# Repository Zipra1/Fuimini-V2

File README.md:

# This design is currently under development.
I do not recommend making this at the moment.
Case is currently not finished, but it should work.

nRF52833 based smol SlimeVR tracker

Design is optimized for manufacturability at medium scales & comfort

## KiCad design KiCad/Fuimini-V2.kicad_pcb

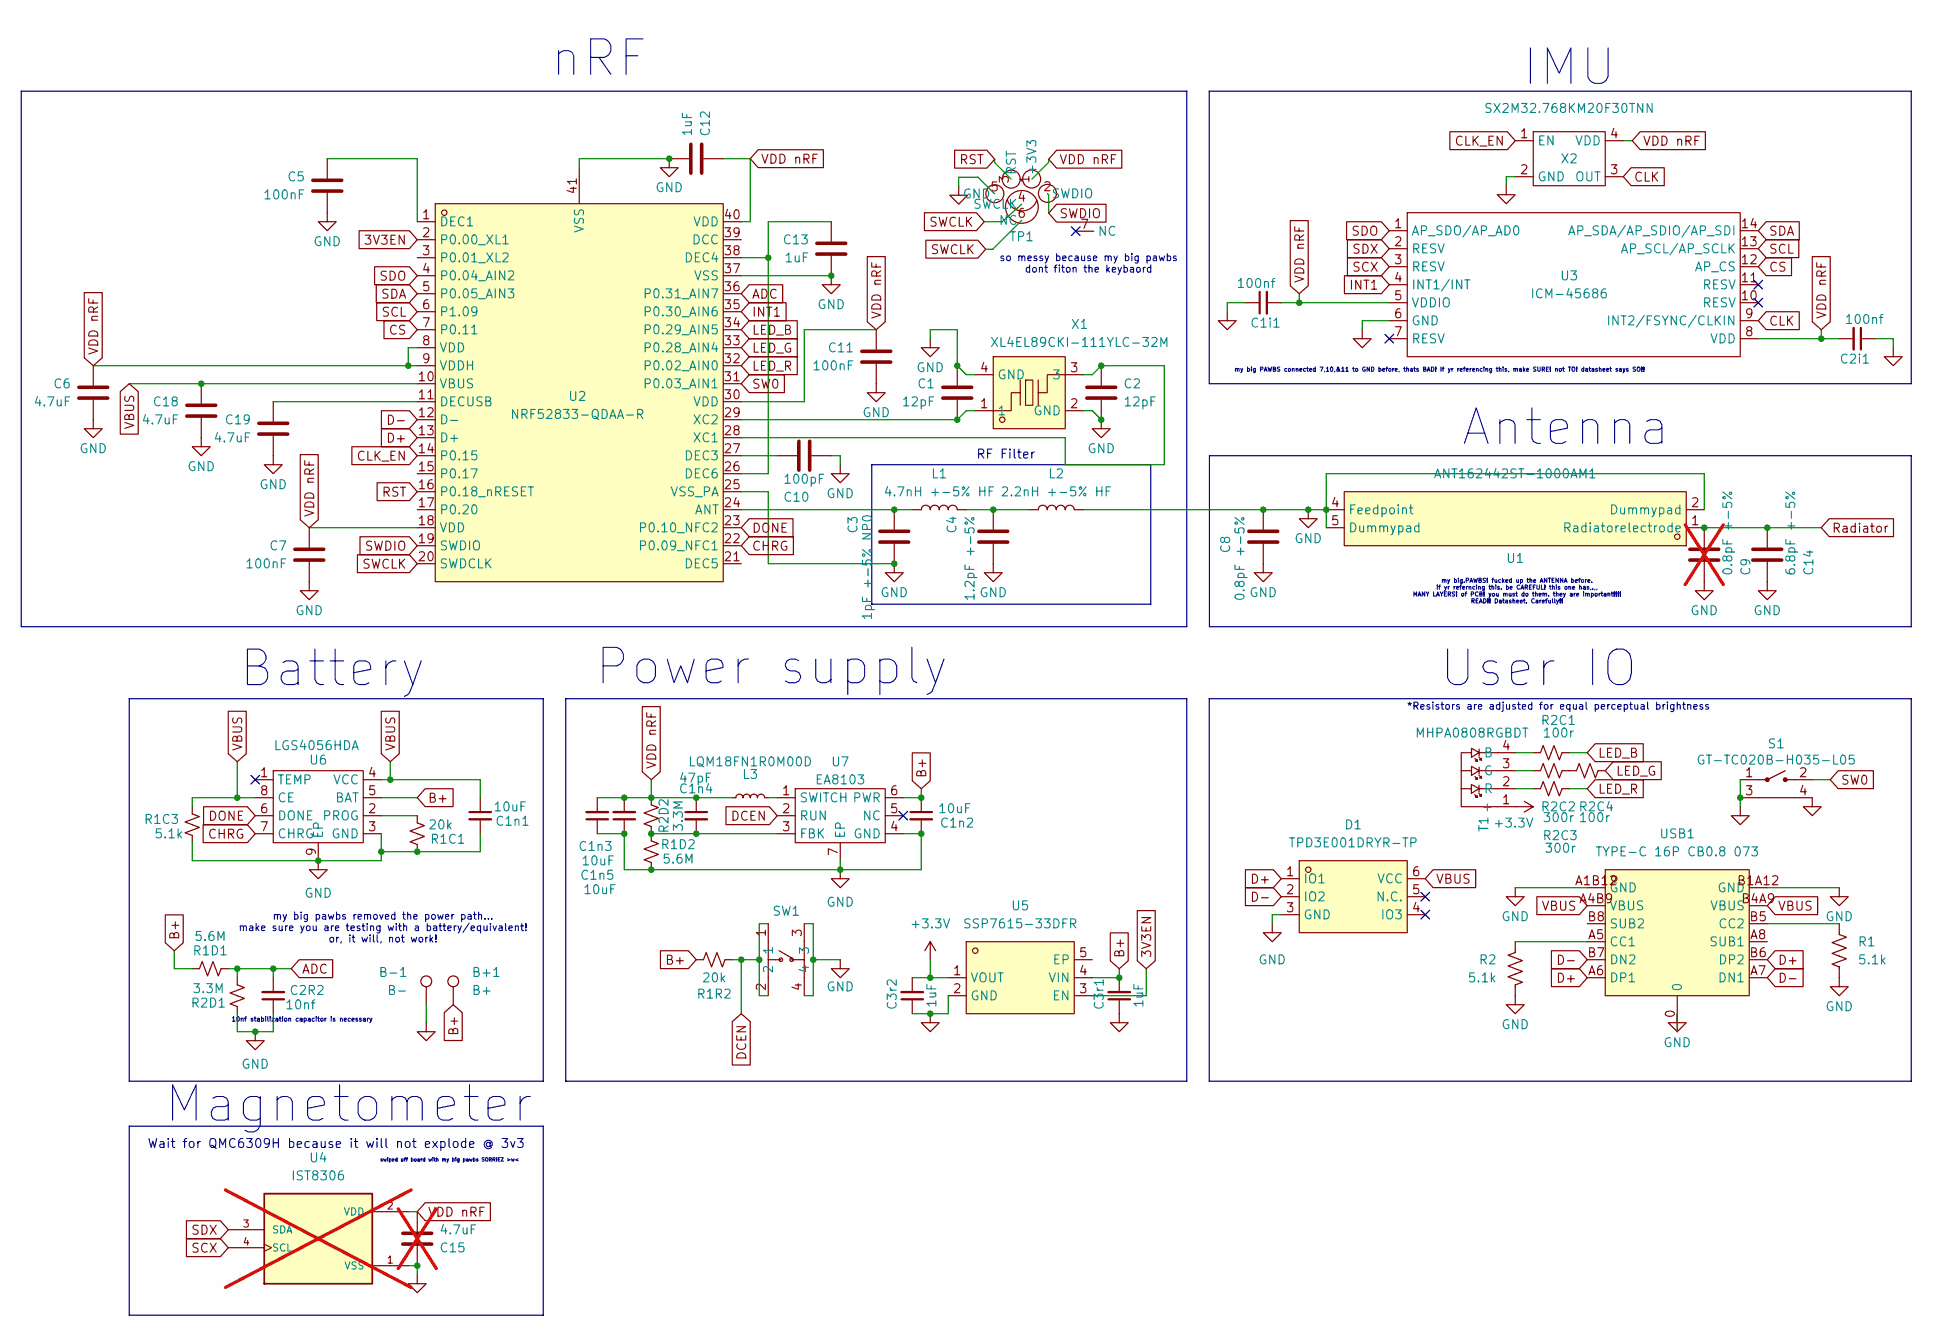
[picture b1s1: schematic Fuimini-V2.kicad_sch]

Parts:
B+1: B+; 2_3-1.5_2.5_1_1
B-1: B-; 2_3-1.5_2.5_1_1
C1, C2: 12pF; C_0201_JLC
C1i1, C2i1: 100nf; C_0201_JLC
C1n1, C1n2, C1n3, C1n5: 10uF; C_0402_JLC
C1n4: 47pF; C_0201_JLC
C2R2: 10nf; C_0201_JLC
C3: 1pF +-5% NP0; C_0201_JLC
C3r1, C3r2, C12, C13: 1uF; C_0201_JLC
C4: 1.2pF +-5%; C_0201_JLC
C5, C7, C11: 100nF; C_0201_JLC
C6, C18, C19: 4.7uF; C_0201_JLC
C8: 0.8pF +-5%; C_0201_JLC
C9: 0.8pF +-5%; C_0201_JLC; not fitted
C10: 100pF; C_0201_JLC
C14: 6.8pF +-5%; C_0201_JLC
C15: 4.7uF; C_0201_JLC; not fitted
D1: TPD3E001DRYR-TP; SON-6_L1.5-W1.0-P0.50-BL_SN74LVC1G19DRYR; LCSC Part C1973987
L1: 4.7nH +-5% HF; L_0201_0603Metric
L2: 2.2nH +-5% HF; L_0201_0603Metric
L3: LQM18FN1R0M00D; L0603
R1, R1C3, R2: 5.1k; R_0201_JLC
R1C1, R1R2: 20k; R_0201_JLC
R1D1, R1D2: 5.6M; R_0201_JLC
R2C1, R2C4: 100r; R_0201_JLC
R2C2, R2C3: 300r; R_0201_JLC
R2D1, R2D2: 3.3M; R_0201_JLC
S1: GT-TC020B-H035-L05; SW-SMD_GT-TC020B-H035-L05
SW1: 1TS026A-1100-0550-CT; SW-SMD_4P-L2.6-W1.6-P0.75-LS3.0; LCSC Part C913779
T1: MHPA0808RGBDT; LED-ARRAY-SMD_4P-L0.80-W0.80-BR
TP1: Paw-Connect_RevB_TC2030-IDC-NL_2x03_P1.27mm_Vertical
U1: ANT162442ST-1000AM1; ANT-SMD_6P-L1.6-W0.8-L; LCSC Part C5119334
U2: NRF52833-QDAA-R; QFN-40_L5.0-W5.0-P0.40-TL-EP3.6; LCSC Part C2895249
U3: ICM-45686; ICM-42688-P
U4: IST8306; PARTREV 1.4; not fitted
U5: SSP7615-33DFR; DFN-4_L1.0-W1.0-P0.65-BL-EP; LCSC Part C3011523
U6: LGS4056HDA; DFN-8_L2.0-W2.0-P0.50-TL-EP1.6
U7: EA8103; DFN-6_L1.5-W1.5-P0.50-BL-EP1.0
USB1: TYPE-C 16P CB0.8 073; USB-C-SMD_TYPE-C-16P-CB0.8-073; LCSC Part C2906289
X1: XL4EL89CKI-111YLC-32M; CRYSTAL-SMD_4P-L1.6-W1.2-BL; LCSC Part C18213028
X2: SX2M32.768KM20F30TNN; Crystal_SMD_2520-4Pin_2.5x2.0mm

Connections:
3V3EN: U2.2 (P0.00_XL1), U5.3 (EN)
+3.3V: C3r2.2, T1.1 (+), U5.1 (VOUT)
ADC: C2R2.2, R1D1.1, R2D1.2, U2.36 (P0.31_AIN7)
B+: B+1.1, C1n2.1, C3r1.2, R1D1.2, R1R2.1, U5.4 (VIN), U6.5 (BAT), U7.6 (PWR)
CHRG: U2.22 (P0.09_NFC1), U6.7 (CHRG)
CLK: U3.9 (INT2/FSYNC/CLKIN), X2.3 (OUT)
CLK_EN: U2.14 (P0.15), X2.1 (EN)
CS: U2.7 (P0.11), U3.12 (AP_CS)
D+: D1.1 (IO1), U2.13 (D+), USB1.A6 (DP1), USB1.B6 (DP2)
D-: D1.2 (IO2), U2.12 (D-), USB1.A7 (DN1), USB1.B7 (DN2)
DCEN: R1R2.2, SW1.1, SW1.2, U7.2 (RUN)
DONE: U2.23 (P0.10_NFC2), U6.6 (DONE)
GND: B-1.1, C1.1, C1i1.1, C1n1.2, C1n2.2, C1n3.1, C1n5.1, C2.2, C2R2.1, C2i1.1, C3.2, C3r1.1, C3r2.1, C4.2, C5.2, C6.2, C7.2, C8.1, C8.2, C9.1, C10.2, C11.2, C12.2, C13.2, C14.1, C15.1, C18.2, C19.2, D1.3 (GND), L2.2, R1.2, R1C1.2, R1C3.1, R1D2.1, R2.2, R2D1.1, S1.1, S1.3, S1.4, SW1.3, SW1.4, TP1.5 (GND), U1.2 (Dummypad), U1.4 (Feedpoint), U1.5 (Dummypad), U2.25 (VSS_PA), U2.37 (VSS), U2.41 (VSS), U3.6 (GND), U4.1 (VSS), U5.2 (GND), U6.3 (GND), U6.9 (EP), U7.4 (GND), U7.7 (EP), USB1.0, USB1.A1B12 (GND), USB1.B1A12 (GND), X1.2 (GND), X1.4 (GND), X2.2 (GND)
INT1: U2.35 (P0.30_AIN6), U3.4 (INT1/INT)
LED_B: R2C1.2, U2.34 (P0.29_AIN5)
LED_G: R2C4.2, U2.33 (P0.28_AIN4)
LED_R: R2C3.2, U2.32 (P0.02_AIN0)
unnamed: C4.1, L1.2, L2.1
unnamed: R2C2.2, R2C4.1
unnamed: R2C1.1, T1.4 (B)
unnamed: R2C2.1, T1.3 (G)
unnamed: R2C3.1, T1.2 (R)
unnamed: C3.1, L1.1, U2.24 (ANT)
unnamed: C5.1, U2.1 (DEC1)
unnamed: C10.1, U2.27 (DEC3)
unnamed: C13.1, U2.26 (DEC6), U2.38 (DEC4)
unnamed: C19.1, U2.11 (DECUSB)
unnamed: C2.1, U2.28 (XC1), X1.3
unnamed: C1.2, U2.29 (XC2), X1.1
unnamed: R1C1.1, U6.2 (PROG)
unnamed: C1n4.2, R1D2.2, R2D2.1, U7.3 (FBK)
unnamed: L3.2, U7.1 (SWITCH)
unnamed: R2.1, USB1.A5 (CC1)
unnamed: R1.1, USB1.B5 (CC2)
RST: TP1.3 (RST), U2.16 (P0.18_nRESET)
Radiator: C9.2, C14.2, U1.1 (Radiatorelectrode)
SCL: U2.6 (P1.09), U3.13 (AP_SCL/AP_SCLK)
SCX: U3.3 (RESV), U4.4 (SCL)
SDA: U2.5 (P0.05_AIN3), U3.14 (AP_SDA/AP_SDIO/AP_SDI)
SDO: U2.4 (P0.04_AIN2), U3.1 (AP_SDO/AP_AD0)
SDX: U3.2 (RESV), U4.3 (SDA)
SW0: S1.2, U2.31 (P0.03_AIN1)
SWCLK: TP1.4 (SWCLK), TP1.6 (NC), U2.20 (SWDCLK)
SWDIO: TP1.2 (SWDIO), U2.19 (SWDIO)
VBUS: C1n1.1, C18.1, D1.6 (VCC), R1C3.2, U2.10 (VBUS), U6.4 (VCC), U6.8 (CE), USB1.A4B9 (VBUS), USB1.B4A9 (VBUS)
VDD nRF: C1i1.2, C1n3.2, C1n4.1, C1n5.2, C2i1.2, C6.1, C7.1, C11.1, C12.1, C15.2, L3.1, R2D2.2, TP1.1 (+3V3), U2.8 (VDD), U2.9 (VDDH), U2.18 (VDD), U2.30 (VDD), U2.40 (VDD), U3.5 (VDDIO), U3.8 (VDD), U4.2 (VDD), X2.4 (VDD)

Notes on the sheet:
10nf stabilization capacitor is necessary
IMU
Magnetometer
Wait for QMC6309H because it will not explode @ 3v3
my big.PAWBS! fucked up the ANTENNA before. if yr referncing this. be CAREFUL! this one has,.,, MANY LAYERS! of PCB! you must do them. they are important!!!! READ!! Datasheet. Carefully!!
my big PAWBS connected 7,10,&11 to GND before, thats BAD! If yr referencing this, make SURE! not TO! datasheet says SO!!
nRF
RF Filter
Battery
User IO
swiped off board with my big pawbs SORRIEZ >w<
*Resistors are adjusted for equal perceptual brightness
Power supply
Antenna
so messy because my big pawbs dont fiton the keybaord
my big pawbs removed the power path... make sure you are testing with a battery/equivalent! or, it will, not work!

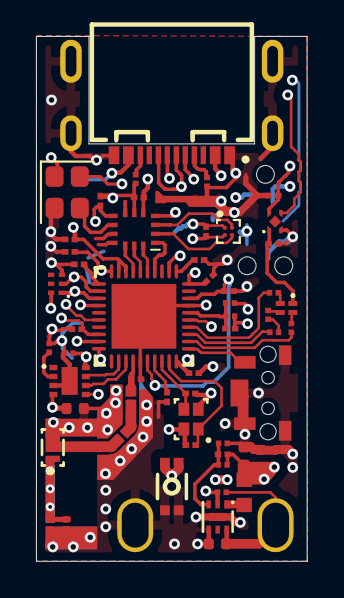
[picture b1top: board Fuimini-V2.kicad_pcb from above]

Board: 4 copper layers, 15.0 x 29.2 mm, 60 parts (1 on the bottom side), 46 nets.

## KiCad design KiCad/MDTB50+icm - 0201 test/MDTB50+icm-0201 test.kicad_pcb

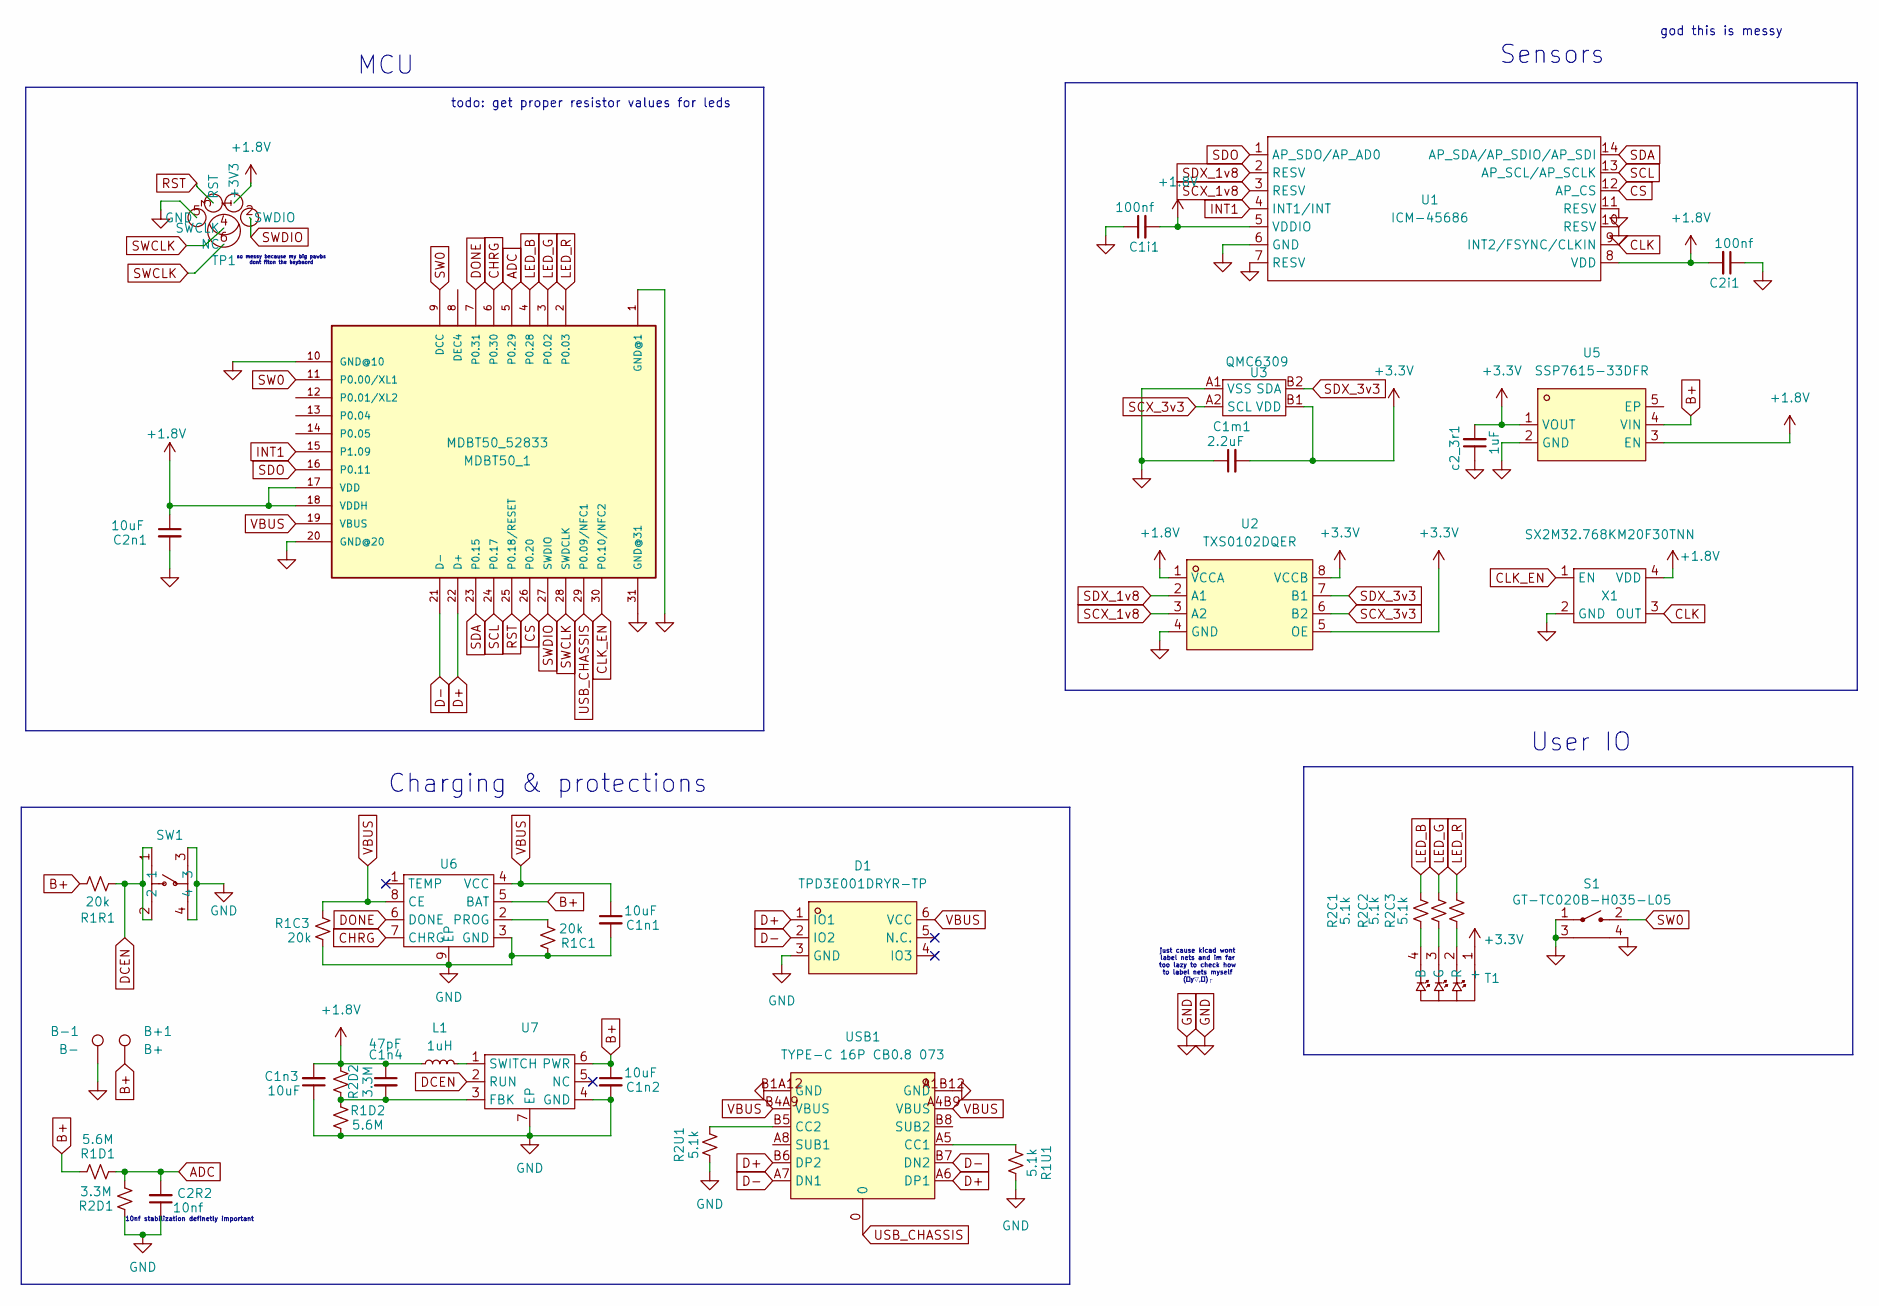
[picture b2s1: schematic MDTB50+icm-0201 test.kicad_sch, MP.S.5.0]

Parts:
B+1: B+; 2_3-1.5_2.5_1_1
B-1: B-; 2_3-1.5_2.5_1_1
C1i1, C2i1: 100nf; C_0201_JLC
C1m1: 2.2uF; C_0201_JLC
C1n1, C1n2, C1n3, C2n1: 10uF; C_0402_JLC
C1n4: 47pF; C_0201_JLC
C2R2: 10nf; C_0201_JLC
D1: TPD3E001DRYR-TP; SON-6_L1.5-W1.0-P0.50-BL_SN74LVC1G19DRYR; LCSC Part C1973987
L1: 1uH; L0603
MDBT50_1: MDBT50_52833; MDBT50
R1C1, R1C3, R1R1: 20k; R_0201_JLC
R1D1, R1D2: 5.6M; R_0201_JLC
R1U1, R2C1, R2C2, R2C3, R2U1: 5.1k; R_0201_JLC
R2D1, R2D2: 3.3M; R_0201_JLC
S1: GT-TC020B-H035-L05
SW1: 1TS026A-1100-0550-CT; SW-SMD_4P-L2.6-W1.6-P0.75-LS3.0; LCSC Part C913779
T1: LED-ARRAY-SMD_4P-L0.80-W0.80-BR
TP1: Paw-Connect_RevA_TC2030-IDC-NL_2x03_P1.27mm_Vertical
U1: ICM-45686; ICM-42688-P
U2: TXS0102DQER; X2SON-8_1.4x1mm_P0.35mm; LCSC Part C2652935
U3: QMC6309
U5: SSP7615-33DFR; DFN-4_L1.0-W1.0-P0.65-BL-EP; LCSC Part C3011523
U6: DFN-8_L2.0-W2.0-P0.50-TL-EP1.6
U7: DFN-6_L1.5-W1.5-P0.50-BL-EP1.0
USB1: TYPE-C 16P CB0.8 073; USB-C-SMD_TYPE-C-16P-CB0.8-073; LCSC Part C2906289
X1: SX2M32.768KM20F30TNN; Crystal_SMD_2520-4Pin_2.5x2.0mm
c2_3r1: 1uF; C_0201_JLC

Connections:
+1.8V: C1i1.2, C1n3.2, C1n4.1, C2i1.2, C2n1.1, L1.1, MDBT50_1.17 (VDD), MDBT50_1.18 (VDDH), R2D2.2, TP1.1 (+3V3), U1.5 (VDDIO), U1.8 (VDD), U2.1 (VCCA), U5.3 (EN), X1.4 (VDD)
+3.3V: C1m1.2, T1.1 (+), U2.5 (OE), U2.8 (VCCB), U3.B1 (VDD), U5.1 (VOUT), c2_3r1.2
ADC: C2R2.2, MDBT50_1.5 (P0.29), R1D1.1, R2D1.2
B+: B+1.1, C1n2.1, R1D1.2, R1R1.1, U5.4 (VIN), U6.5 (BAT), U7.6 (PWR)
CHRG: MDBT50_1.6 (P0.30), U6.7 (CHRG)
CLK: U1.9 (INT2/FSYNC/CLKIN), X1.3 (OUT)
CLK_EN: MDBT50_1.30 (P0.10/NFC2), X1.1 (EN)
CS: MDBT50_1.26 (P0.20), U1.12 (AP_CS)
D+: D1.1 (IO1), MDBT50_1.22 (D+), USB1.A6 (DP1), USB1.B6 (DP2)
D-: D1.2 (IO2), MDBT50_1.21 (D-), USB1.A7 (DN1), USB1.B7 (DN2)
DCEN: R1R1.2, SW1.1, SW1.2, U7.2 (RUN)
DONE: MDBT50_1.7 (P0.31), U6.6 (DONE)
GND: B-1.1, C1i1.1, C1m1.1, C1n1.2, C1n2.2, C1n3.1, C2R2.1, C2i1.1, C2n1.2, D1.3 (GND), MDBT50_1.1 (GND@1), MDBT50_1.10 (GND@10), MDBT50_1.20 (GND@20), MDBT50_1.31 (GND@31), R1C1.2, R1C3.1, R1D2.1, R1U1.2, R2D1.1, R2U1.1, S1.1, S1.3, S1.4, SW1.3, SW1.4, TP1.5 (GND), U1.6 (GND), U1.7 (RESV), U1.10 (RESV), U1.11 (RESV), U2.4 (GND), U3.A1 (VSS), U5.2 (GND), U6.3 (GND), U6.9 (EP), U7.4 (GND), U7.7 (EP), USB1.A1B12 (GND), USB1.B1A12 (GND), X1.2 (GND), c2_3r1.1
INT1: MDBT50_1.15 (P1.09), U1.4 (INT1/INT)
LED_B: MDBT50_1.4 (P0.28), R2C1.2
LED_G: MDBT50_1.3 (P0.02), R2C2.2
LED_R: MDBT50_1.2 (P0.03), R2C3.2
unnamed: R2C1.1, T1.4 (B)
unnamed: R2C2.1, T1.3 (G)
unnamed: R2C3.1, T1.2 (R)
unnamed: R1C1.1, U6.2 (PROG)
unnamed: C1n4.2, R1D2.2, R2D2.1, U7.3 (FBK)
unnamed: L1.2, U7.1 (SWITCH)
unnamed: R1U1.1, USB1.A5 (CC1)
unnamed: R2U1.2, USB1.B5 (CC2)
RST: MDBT50_1.25 (P0.18/RESET), TP1.3 (RST)
SCL: MDBT50_1.24 (P0.17), U1.13 (AP_SCL/AP_SCLK)
SCX_1v8: U1.3 (RESV), U2.3 (A2)
SCX_3v3: U2.6 (B2), U3.A2 (SCL)
SDA: MDBT50_1.23 (P0.15), U1.14 (AP_SDA/AP_SDIO/AP_SDI)
SDO: MDBT50_1.16 (P0.11), U1.1 (AP_SDO/AP_AD0)
SDX_1v8: U1.2 (RESV), U2.2 (A1)
SDX_3v3: U2.7 (B1), U3.B2 (SDA)
SW0: MDBT50_1.9 (DCC), MDBT50_1.11 (P0.00/XL1), S1.2
SWCLK: MDBT50_1.28 (SWDCLK), TP1.4 (SWCLK), TP1.6 (NC)
SWDIO: MDBT50_1.27 (SWDIO), TP1.2 (SWDIO)
USB_CHASSIS: MDBT50_1.29 (P0.09/NFC1), USB1.0
VBUS: C1n1.1, D1.6 (VCC), MDBT50_1.19 (VBUS), R1C3.2, U6.4 (VCC), U6.8 (CE), USB1.A4B9 (VBUS), USB1.B4A9 (VBUS)

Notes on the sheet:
todo: get proper resistor values for leds
Charging & protections
Sensors
just cause kicad wont label nets and im far too lazy to check how to label nets myself (￣y▽,￣)╭
MCU
so messy because my big pawbs dont fiton the keybaord
User IO
god this is messy
10nf stabilization definetly important

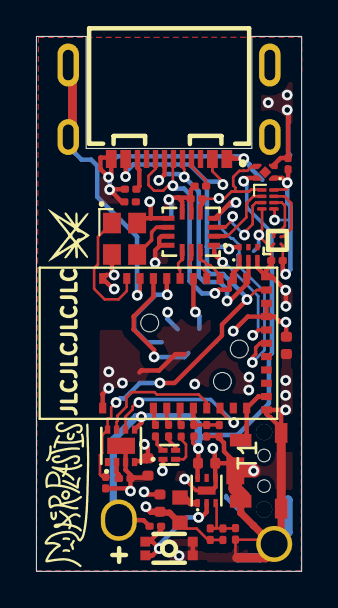
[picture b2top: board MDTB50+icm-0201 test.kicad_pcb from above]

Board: 4 copper layers, 14.7 x 29.7 mm, 39 parts (1 on the bottom side), 38 nets.

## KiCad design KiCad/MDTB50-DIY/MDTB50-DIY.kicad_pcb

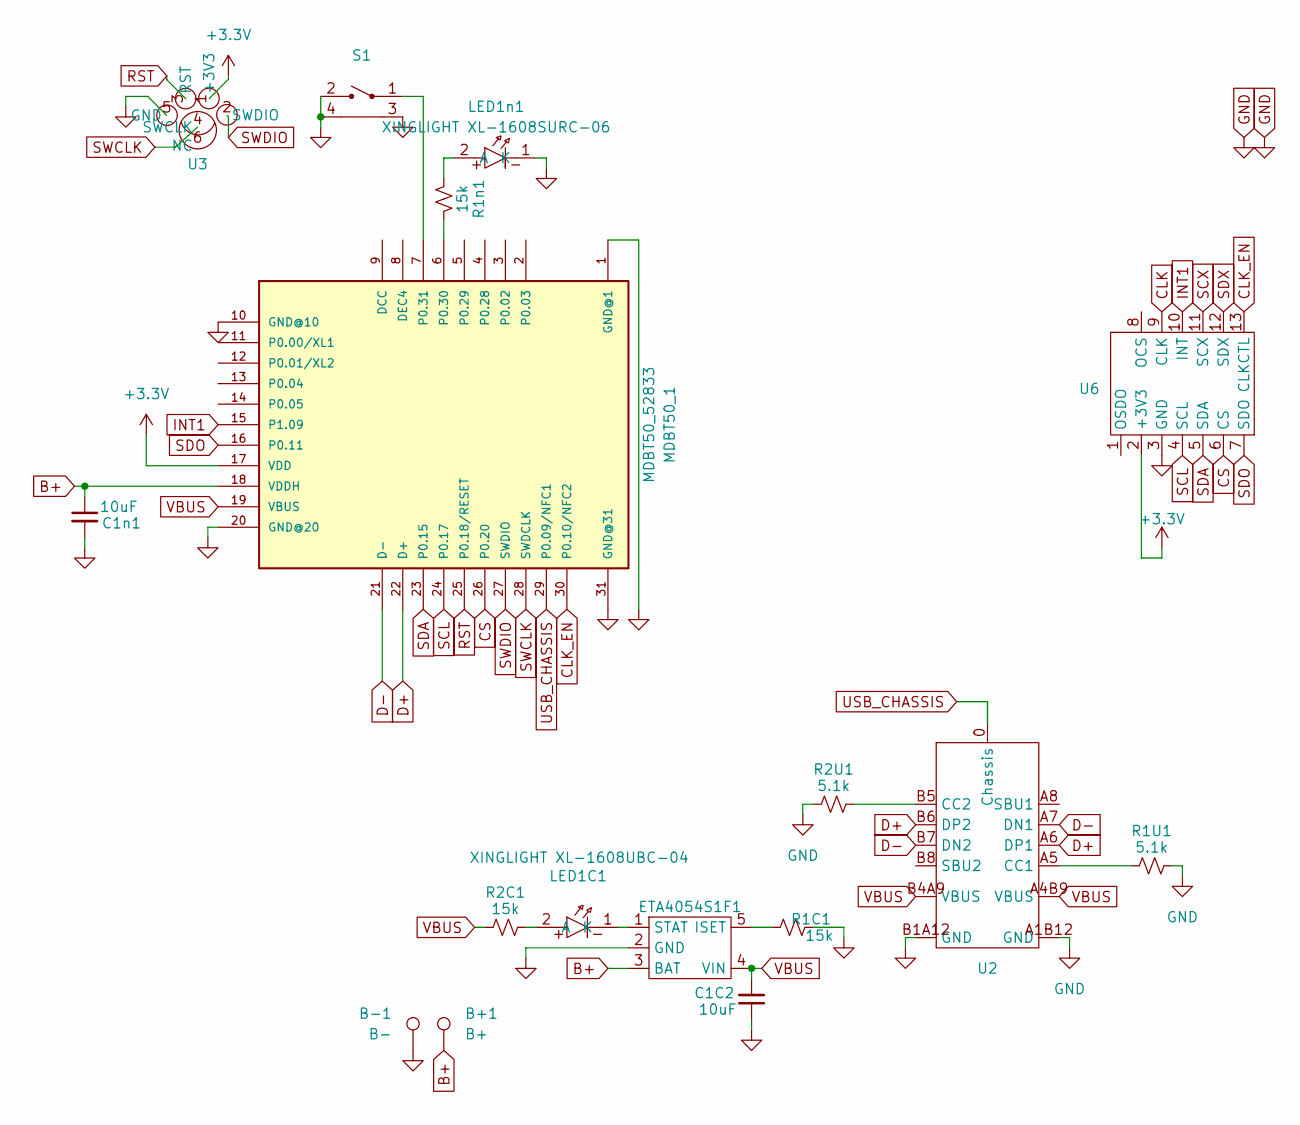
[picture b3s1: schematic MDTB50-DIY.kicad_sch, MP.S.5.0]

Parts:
B+1: B+; 2_3-1.5_2.5_1_1
B-1: B-; 2_3-1.5_2.5_1_1
C1C2, C1n1: 10uF; C_0402_JLC
ETA4054S1F1: ETA4054S2F
LED1C1: XINGLIGHT XL-1608UBC-04
LED1n1: XINGLIGHT XL-1608SURC-06; XINGLIGHT XL-1608UBC-04
MDBT50_1: MDBT50_52833; MDBT50
R1C1, R1n1, R2C1: 15k; R_0402_JLC
R1U1, R2U1: 5.1k; R_0402_JLC
S1: GT-TC020B-H035-L05
U2: HCTL HC-TYPE-C-16P-CB1.0
U3: Paw-Connect_RevA_TC2030-IDC-NL_2x03_P1.27mm_Vertical
U6: kounolab-imu

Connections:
+3.3V: MDBT50_1.17 (VDD), U3.1 (+3V3), U6.2 (+3V3)
B+: B+1.1, C1n1.1, ETA4054S1F1.3 (BAT), MDBT50_1.18 (VDDH)
CLK: U6.9 (CLK)
CLK_EN: MDBT50_1.30 (P0.10/NFC2), U6.13 (CLKCTL)
CS: MDBT50_1.26 (P0.20), U6.6 (CS)
D+: MDBT50_1.22 (D+), U2.A6 (DP1), U2.B6 (DP2)
D-: MDBT50_1.21 (D-), U2.A7 (DN1), U2.B7 (DN2)
GND: B-1.1, C1C2.1, C1n1.2, ETA4054S1F1.2 (GND), LED1n1.1 (K), MDBT50_1.1 (GND@1), MDBT50_1.10 (GND@10), MDBT50_1.20 (GND@20), MDBT50_1.31 (GND@31), R1C1.2, R1U1.2, R2U1.1, S1.2, S1.3, S1.4, U2.A1B12 (GND), U2.B1A12 (GND), U3.5 (GND), U6.3 (GND)
INT1: MDBT50_1.15 (P1.09), U6.10 (INT)
unnamed: ETA4054S1F1.5 (ISET), R1C1.1
unnamed: ETA4054S1F1.1 (STAT), LED1C1.1 (K)
unnamed: LED1C1.2 (A), R2C1.2
unnamed: LED1n1.2 (A), R1n1.2
unnamed: MDBT50_1.6 (P0.30), R1n1.1
unnamed: MDBT50_1.7 (P0.31), S1.1
unnamed: R1U1.1, U2.A5 (CC1)
unnamed: R2U1.2, U2.B5 (CC2)
RST: MDBT50_1.25 (P0.18/RESET), U3.3 (RST)
SCL: MDBT50_1.24 (P0.17), U6.4 (SCL)
SCX: U6.11 (SCX)
SDA: MDBT50_1.23 (P0.15), U6.5 (SDA)
SDO: MDBT50_1.16 (P0.11), U6.7 (SDO)
SDX: U6.12 (SDX)
SWCLK: MDBT50_1.28 (SWDCLK), U3.4 (SWCLK), U3.6 (NC)
SWDIO: MDBT50_1.27 (SWDIO), U3.2 (SWDIO)
USB_CHASSIS: MDBT50_1.29 (P0.09/NFC1), U2.0 (Chassis)
VBUS: C1C2.2, ETA4054S1F1.4 (VIN), MDBT50_1.19 (VBUS), R2C1.1, U2.A4B9 (VBUS), U2.B4A9 (VBUS)

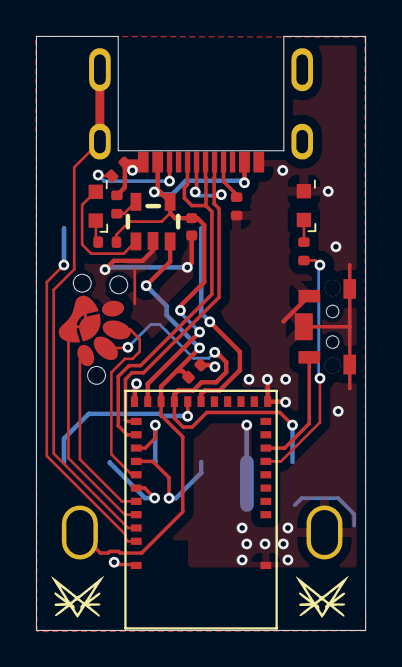
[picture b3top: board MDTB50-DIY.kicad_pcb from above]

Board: 2 copper layers, 18.3 x 33.0 mm, 17 parts (1 on the bottom side), 24 nets.

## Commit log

2025-06-07 Added KiCad files
2025-06-07 - edited readme.md
2025-06-11 - Added DIY pcb (unfinished) - Edited README.md
2025-06-12 - Started redoing layout for DIY variant
2025-06-14 - DIY PCB fully routed. But it kinda sucks.
2025-06-17 - Changed PCB to 4 layer - Added QMC6309 magnetometer
2025-06-19 - Finished back silkscreen for high volume version
2025-06-30 - Added external 1.8v regulator, external 3.3v regulator, QMC6309, logic level shifter for QMC6309, pushbutton power disconnect - Replaced USB C port for better one
2025-06-30 - Added ESD protection
2025-07-06 - No more non 90deg angles on components. Yay.
2025-08-05 - Added 0201 version with: DCDC, RGB LED, replaced charger IC, shortened by 2mm.
2025-10-03 - Changed MDBT50-P512K to bare nRF52833 chip. - Updated README
2025-10-10 - Added test points for VBUS and VDD
2025-10-10 - Added "CERN OHL v2 - Strongly Reciprocal" license
2025-10-27 - Updated case models
2025-11-16 - Moved IMU decoupling caps closer to IMU - Updated IMU footprint - Smoothed 2.4GHz RF trace - Disconnected 2.4GHz RF reference gnd from main gnd plane - Connected nRF pin 37 (gnd) to center ground p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
2025-12-10 - Updated PCB dont remember what (￣y▽,￣)╭ - Updated case design dont remember what (/▽＼)
2025-12-10 - Updated README
2025-12-21 - Added device files for building own firmware
2025-12-30 - Improved fitment, added PCB strain relief, improved button clickiness, changed battery size (blehhh didn't really want to but need 2)
